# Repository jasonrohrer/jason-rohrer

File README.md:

# jason-rohrer
A repository for my non-project work.

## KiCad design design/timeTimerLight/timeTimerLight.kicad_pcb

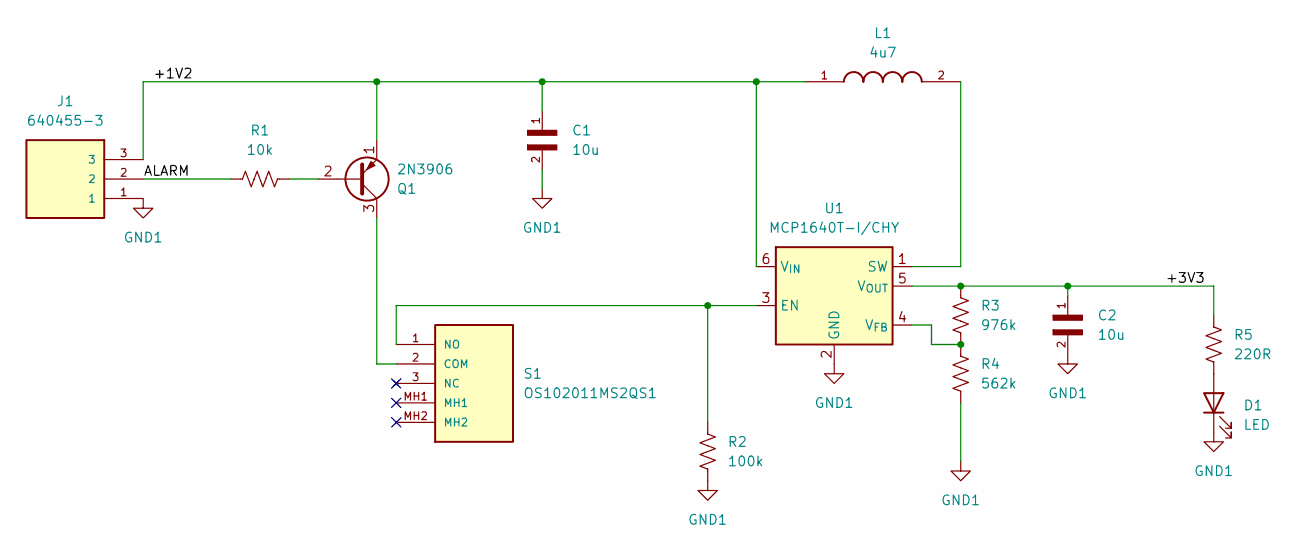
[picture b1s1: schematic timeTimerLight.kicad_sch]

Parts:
C1, C2: 10u; CAPRB250W50L400T250H550; PARTREV 20151209; DigiKey_Part_Number 445-FK18X5R0J106MR020-ND
D1: LED; LED_D5.0mm
J1: 640455-3; TE_640455-3; PARTREV R
L1: 4u7; IND_CDRH2D18_HPNP-4R7NC; PARTREV 7-Jan-14; DigiKey_Part_Number 308-2297-1-ND
Q1: 2N3906; TO-92_Inline
R1: 10k; RESAD1100W55L630D240B
R2: 100k; RESAD1100W55L630D240B
R3: 976k; RESAD1100W55L630D240B
R4: 562k; RESAD1100W55L630D240B
R5: 220R; RESAD1100W55L630D240B
S1: OS102011MS2QS1; MOUSER_PART_NUMBER 611-OS102011MS2QS1; DigiKey_Part_Number CKN9542-ND
U1: MCP1640T-I/CHY; SOT-23-6

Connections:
/+1V2: C1.1, J1.3, L1.1, Q1.1 (E), U1.6 (V_{IN})
/+3V3: C2.1, R3.1, R5.1, U1.5 (V_{OUT})
/ALARM: J1.2, R1.2
GND1: C1.2, C2.2, D1.1 (K), J1.1, R2.2, R4.2, U1.2 (GND)
unnamed: D1.2 (A), R5.2
unnamed: Q1.2 (B), R1.1
unnamed: Q1.3 (C), S1.2 (COM)
unnamed: R2.1, S1.1 (NO), U1.3 (EN)
unnamed: L1.2, U1.1 (SW)
unnamed: R3.2, R4.1, U1.4 (V_{FB})

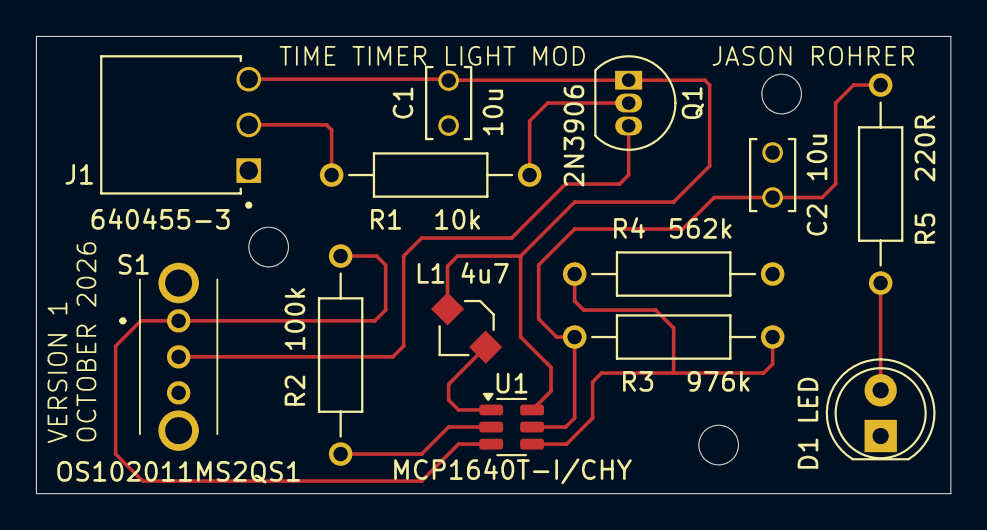
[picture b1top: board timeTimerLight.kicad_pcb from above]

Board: 2 copper layers, 50.8 x 25.4 mm, 13 parts (0 on the bottom side), 10 nets.

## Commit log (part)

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2020-01-05 Fixed another bug in parsing folder of input files.
2020-01-05 Parameter which allows chapter sub-headers.
2020-01-05 Testing wrong var.
2020-01-06 Processing chapter sub-headings to make them all uniformly uppercase.
2020-01-06 Chapter sub-head processing was breaking up words, thus removing some exra spaces that occur in the input text.
2020-01-06 Oz title script.
2020-01-06 Wayward space
2020-01-06 Word limit as parameters.
2020-01-07 Added check for degen case with one very long word (in trials, got 00000000... as output once).
2020-01-07 Special case for epilogue.
2020-01-07 No period in mockingbird chapter headers.
2020-01-07 Detection of short sentences that are actually chapter sub-headers.
2020-01-08 Typo
2020-01-09 Fixed variable file name.
2020-01-09 Requiring at least 3 occurrences of each required word found in tail of seed file in output.
2020-01-12 Required word checking was too strict, and mockingbird gen got stuck on chapter 5. Loosening it.
2020-01-15 Join script fixes weird '' quote marks.
2020-01-15 Typo.
2020-01-21 Added version of main novel generation script for 2k-3k chapters, and only 18 chapters.
2020-01-30 Experimenting with sub-1200-word chapters.
2020-02-13 Trying whole-cloth for AI to generate start of novel.
2020-02-13 100 words instead of 50.
2020-02-27 300 words from 10 hand-picked seeds.
2020-02-27 Script for printing longer runs together.
2020-05-26 Added u-joint.
2020-07-04 Ask for 100 chars (the minimum billable amount) per request.
2020-07-04 Allow multiple lines in computer response.
2020-07-04 Start new chat link at top
2020-07-05 Added support for square brackets in chat.
2020-07-05 Whoops, messed up prefix measuring code.
2020-07-22 Final tweaks to get it working with coreweave transformer.
2020-08-07 Final plot script, plus copy-to-clipboard PNG output.
2020-08-31 Working on moving live HTML for homepage away from UCSC CVS. Adding pages from live site as-needed.
2020-09-03 PD released.
2021-01-15 With 2 layers of sheetrock, hat channels can be spaced 24 inches apart, not 16.
2021-01-16 Working on kitchen layout.
2021-01-17 Matte samples.
2021-01-21 Drawing from Acoustical Surfaces.
2021-01-26 Tile square footage test.
2021-03-12 Latest measurements in place.
2021-03-13 Working on island.
2021-03-19 Added fridge and freezer.
2021-03-19 More cabinet design.
2021-03-23 Added range feet positions and feet measurements.
2021-03-24 30 inch res fridge and freezer. Kitchenaid dishwasher. Separated equipment into layers.
2021-03-24 Working on layout of sink.
2021-03-25 Sink in place, more door and drawer clearances.
2021-03-26 Window inner frame bars.
2021-03-26 Tower cabinet by fridge, working on second island.
2021-03-26 Working on rotated island attempt.
2021-03-27 Cabinet handles on front view.
2021-03-27 Added true faucet DXF info to front view of kitchen.
2021-03-27 Side wall cabinets in front view.
2021-03-27 Added MUA vent location.
2021-03-28 Island layout done. Working on pushing wall cabinets into separate layer.
2021-03-28 Got rid of tower next to fridges, for now.
2021-03-28 Converted extra sink base into standard drawer/cupboard base.
2021-03-28 Side view mostly done.
2021-03-28 Got rid of working junk. Side oven door now in hatch layer.
2021-03-28 More fridge views.
2021-03-28 Fridge DWG files.
2021-03-29 Moved stove front view to better location in grid.
2021-03-29 Moved B33 label down for redability.
2021-04-02 Added measurments for faucet holes.
2021-04-06 Measurements for wall cabinet pair.
2021-04-07 Tweaked.
2021-04-09 Key plan mostly done.
2021-04-09 Garage key can access mudroom.
2021-04-09 Start of lock order in spreadsheet.
2021-04-15 Location of gas pipe.
2021-04-30 Notes on deep card games.
2021-07-16 Working on c version of binary game min-max AI. Currently profiling it.
2021-07-16 Dramatic speed-up through profiling, no longer copying vectors during tree search. Back to interactive mode, fixed bug of premature end when one column emptied.
2021-07-17 Got brute-force search for games with interesting first-move choices working.
2021-07-20 Added positional measurements for cabinets.
2021-07-30 Previous version of support-my-work, with link to donate by mail.
2021-08-06 Working on precise layout for sink cabinet.
2021-08-06 Dishwasher hole in place.
2021-08-07 Base visibility.
2022-03-15 Cron job to record 10-minute video segments.
2022-03-15 Other cron scripts.
2022-03-16 Every 20 seconds instead of ever 30 seconds for snaps.
2022-03-16 Keyboard 1,2,3 for switching primary camera view, for integration with USB controller in future.
2022-03-16 got rid of FPS filter.
2022-03-16 Motion detection spread out over periodic snaps calls. Building motion timelapse nightly during daily call.
2022-03-18 Deleting files older than 30 days.
2022-05-03 Fixed escapist links.
2022-08-26 Auto-sleep dashboard after 5 idle minutes to save bandwidth when no one is looking.
2022-09-22 Fixed size on click.
2023-01-11 Updated to link to reprojector.
2023-01-31 Links to real-world games, including skydrop. Simulate the dead.
2023-04-04 Layout mostly finished on template.
2023-04-04 Rounded tips of mountain graphic
2023-04-06 Elevation plot kindof working. Still need proper scaling based on distance between start and end points.
2023-04-06 Changed to thinner Avenir font for mountain name. Centered mountain name. Added elevation label.
2023-04-06 Notes about how to import SVG elevation plots.
2023-04-06 Latest elevation to SVG code. Working well. Takes distance in miles now.
2023-04-06 Spaced lines on mountain name.
2023-04-06 Parker elevation export.
2023-04-12 Neville Peak badges.
2023-05-15 Badges for Belknap hike.
2023-06-06 Mailbox placement mock-up.
2023-06-20 Tokens for Prospect and Big Ball.
2023-07-22 Address in Futura Bold and split into DXF parts.
2023-07-30 Caslon version of address.
2023-07-30 Got basic scad extrusion working, but need newer version to be able to control facets of import.
2023-07-31 Turned off working scaling.
2023-07-31 Increased hole diameter by 0.015 after test print was too tight for magnets.
2023-08-16 Survey results.
2023-09-17 Crank hole, with rotating part, working. Main ring still not quite big enough to fit over FIZ knob.
2023-09-17 Have diameter tweak for big hole fitting knob snugly.
2023-09-18 Decided to drop the idea of a rotating crank knob. First main print didn't work and it was seized up. Also, made arm much lighter (first main print had too much weight, arm would rotate on its own).
2023-11-04 Added front drive camera to dashboard.
2023-11-04 Added frontDrive camera to user crontab.
2023-11-04 Fixed so that if one image fails to load, whole update doesn't stall for longer than 2 seconds total.
2023-11-15 3 more cameras added to cronjob.
2023-11-29 Added potential chase walls and clearances.
2024-01-24 Ayza's 3D-printed shelf hook.
2024-05-06 Support for second transcript (for Ayza), and also specifying school name and location.
2024-05-14 Notes about de-interlacing and frame-rate converting Mez's camcorder footage.
2024-06-04 Screw holes in mounting plate for AC/DC converters.
2024-07-22 Working on remote camera push script.
2024-08-05 Index for remote camera web viewer.
2024-08-11 Templates for lining up wood stove with 2nd floor hole.
2024-08-21 Exported separate SVGs of skull.
2024-08-21 Teeth no longer overlap.
2024-08-22 Thickened etched lines by 3x.
2024-08-22 Etched lines closer to now-lower side teeth.
2024-08-22 Bigger gap between smiling teeth.
2024-08-22 More consistent gap width between upper and lower teeth.
2024-08-22 Added outside ridge around skull.
2024-08-22 Working on coin rim and text.
2024-08-22 First pass of coin design done.
2024-08-22 Skull text to separate layer.
2024-08-22 Whoops, wrong font on bottom of rim text.
2024-08-22 Updated versions of all separate SVG exports.
2024-08-22 Sprue connection point template.
2024-08-22 Sprue points along rims
2024-08-22 Working on sprues... still not quite right.
2024-08-22 Added re-centered SVG layer files, and sprue point files.
2024-08-23 Final volume plugged in.
2024-08-25 Overpass font spacing looking good on skull text.
2024-08-25 SVG exports of Overpass versions of text.
2024-08-25 Centered new Overpass font in coin rim, since font was shorter, and it looked off. After re-centering, adjusted character and word spacing again, so top and bottom phrases match, and fixed rotation.
2024-08-26 Overpass versions of fonts in OpenSCAD.
2024-08-26 Wider skull text export.
2024-08-26 Added separate single sprue for coin.
2024-08-30 New more delicate sprue pattern, trying to avoid having letters break off.
2024-09-13 Final version. Text hidden for engraving after casting. Flipped to cast face-down.
2024-11-05 Bottom cross beam for holding log joists.
2024-11-25 Added SideYardFront camera, 9th camera, to dashboard.
2024-11-25 Dashboard has all 13 cameras now.
2024-11-25 Remote camera view scripts and site now handle all 13 cameras.
2024-12-02 Fixed some broken links. Added skydrop to release log.
2025-01-21 Measurements to show that smallest domino won't poke through.
2025-02-22 Transparent version of signature.
2025-04-01 Ayza updated transcript, spring 2025.
2025-04-18 Added support to video-recording script to accept one extra parameter (optional), 1 or 0, to record audio. Only some cameras seem to support the audio stream. Not sure why.
2025-04-27 Version 2, with shorter sidewalls and top/bottom walls.
2025-04-27 Version 4, with rounded-corner and equal thickness frame.
2025-05-13 Page setup for printing wood cut-out.
2025-05-19 Better shape, but this one is too tight on shaft.
2025-05-19 Fits shaft, but not balanced and wants to fall off. Made legs slightly longer, and made connecting bridge thinner.
2025-05-20 Got imported into OpenSCAD, with curves for text.
2025-05-20 Radius guage finally ready for print. Font thick enough, and lettering far enough away from edge.
2025-05-20 Reference lines.
2025-05-20 Better facet size for font appearance.
2025-05-22 Better bottom profile, shorter on one leg. 3-hole magnet hole placement to stop sliding.
2025-05-25 Added resting lip beneath tip rim of fan.
2025-05-25 Tweaks... added a ledge for fan rim to sit on, switched to face-down orientation (back is curved). Made a test print of part of this model, and Kestrel held in place nice and flat.
2025-05-26 Measurements from clean/dirty Rikon with 4'' hose on various tools.
2025-06-02 Not sure what changes weren't checked in...
2025-06-14 Added measurements on 5 inch pipe.
2025-07-06 Added -y to timelapse script to allow ffmpeg to auto-replace files, in case they were manually generated mid-day.
2025-08-06 Moved Ko-ken stuff into sub-folder. Cloned files to start working on feet for larger 3/8 inch drive case.
2025-08-07 Got end that will fit on caliper done for testing.
2025-08-07 Flipped opening.
2025-08-07 Tweaked size of openings more.
2025-08-07 Still tweaking fitment. Getting close.
2025-08-08 Finally got fitment correct on end of caliper.
2025-08-08 Got legs to line up and union with end cover to make a printable object.
2025-08-08 Smaller test print of subsection.
2025-08-09 Got new corner radius, 5/8, in place. Re-parameterized magnet hole positions based on corner radius.
2025-08-11 Working on big hole positioning.
2025-08-22 Working on poster for teen group.
2025-08-24 Fixed name on tear-offs for teen poster.
2025-09-26 Working on bit holder in Solidworks
2025-09-28 Assembly completely done. Have exported version of base with corner mini fillets to line up with fillets on bit holders.
2025-09-29 Added hex holes in backer base to use less material and take less time to print. It also gives you back access when trying to slide out bits that are in the middle.
2025-09-29 Instructions complete with oil change log.
2025-09-30 Rounded exterior corners more. Half-holder has one less slot to make room for 6 long bits in full holder.
2026-01-16 Switched to OHOL for release list.
2026-02-04 Added Novy transcript.
2026-03-11 Added lpr camera to dashboard.
2026-03-11 Fixed bash-specific compare
